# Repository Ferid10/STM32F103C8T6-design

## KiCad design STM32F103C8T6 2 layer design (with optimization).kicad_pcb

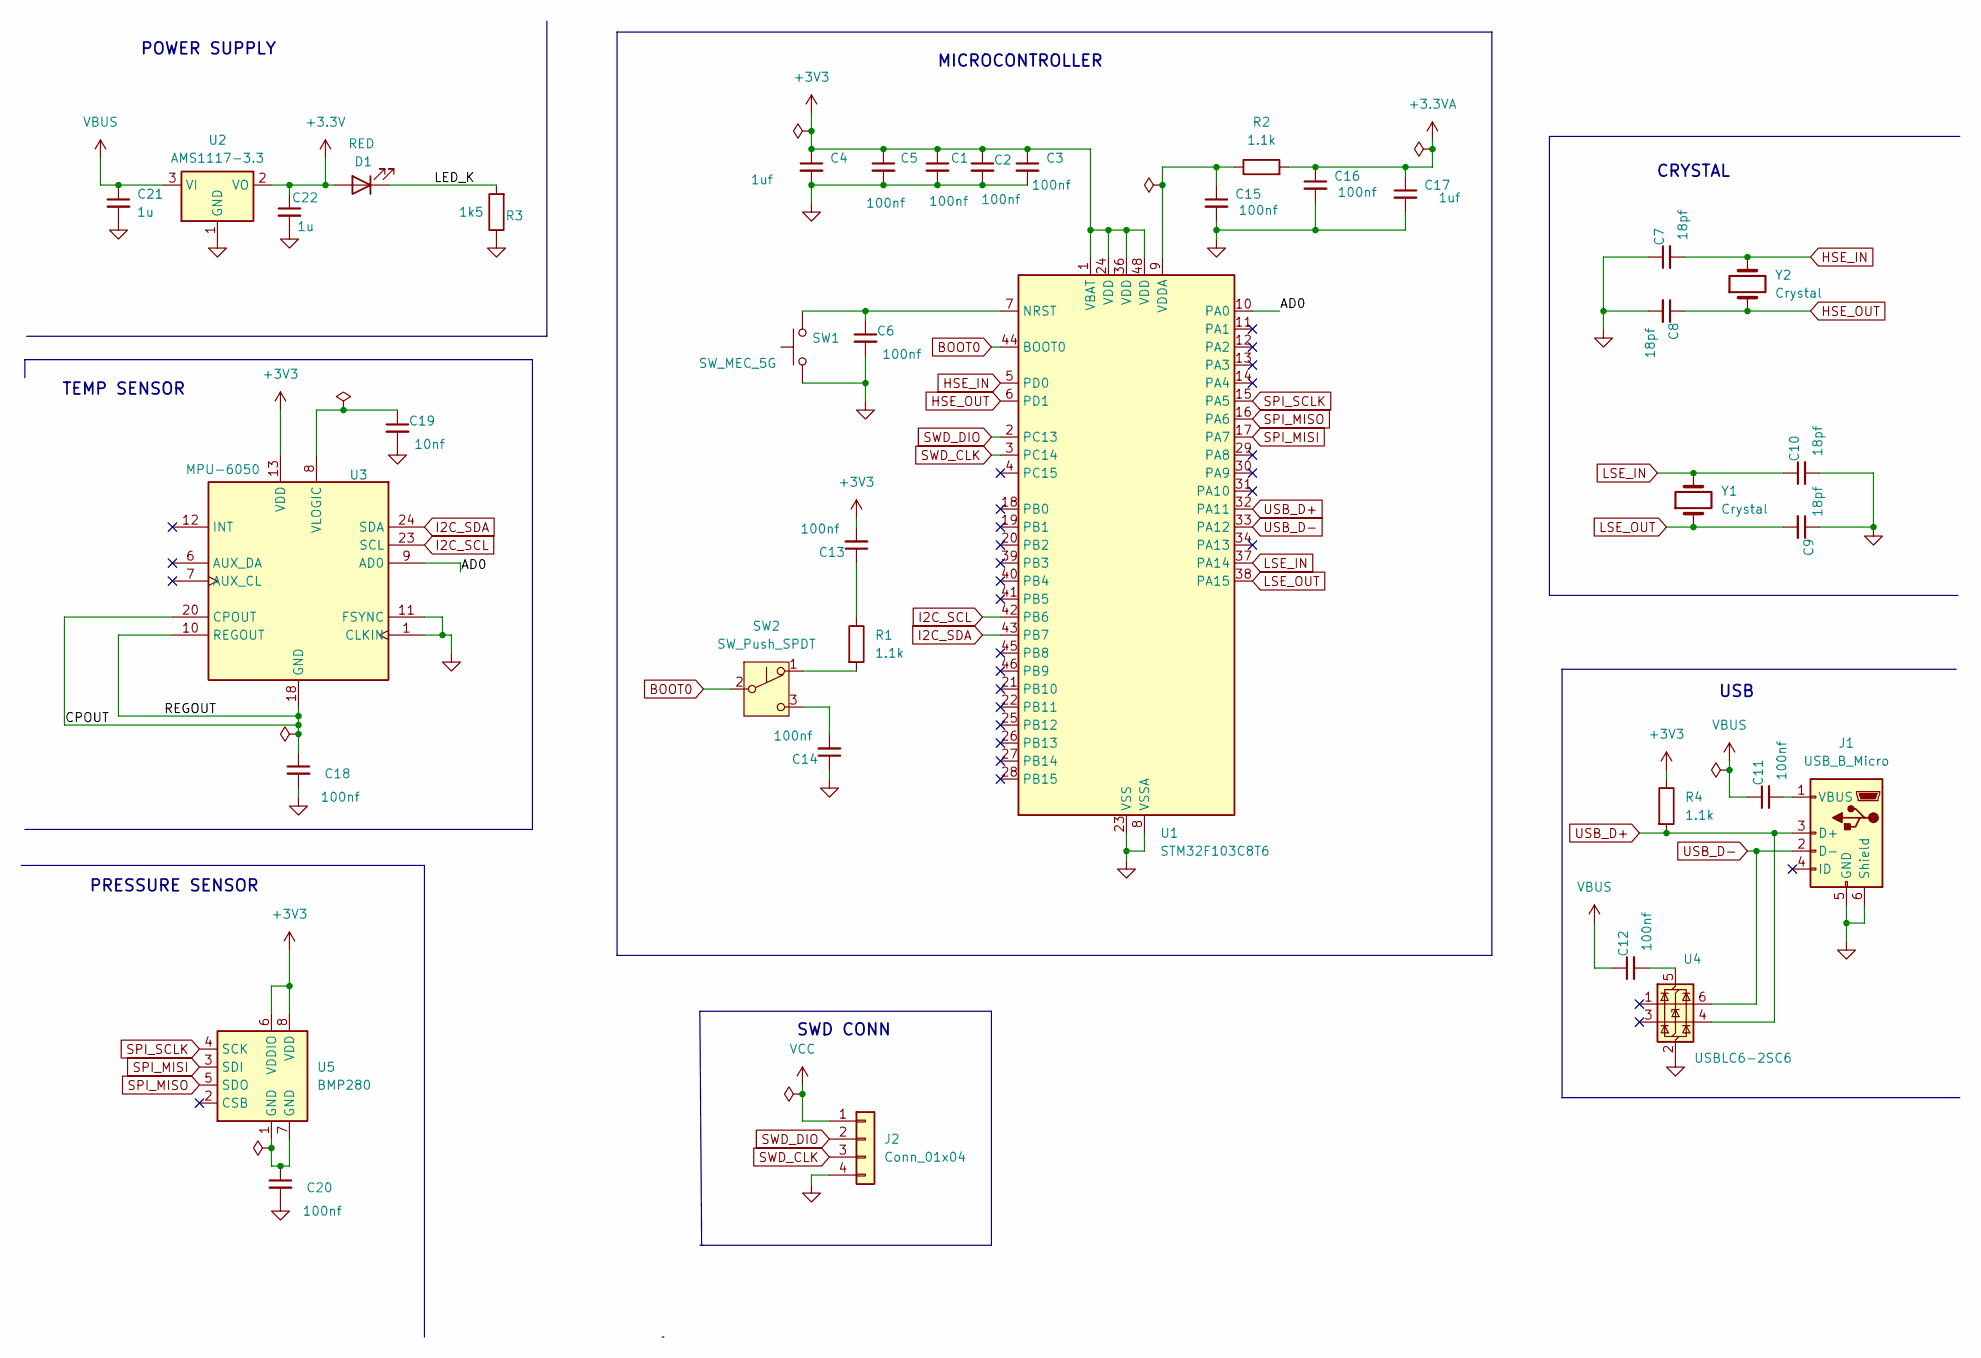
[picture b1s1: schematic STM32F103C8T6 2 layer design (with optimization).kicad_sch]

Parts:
C1, C2, C3, C5, C6, C11, C12, C13, C14, C15, C16: 100nf; C_01005_0402Metric
C4, C17: 1uf; C_0201_0603Metric
C7, C8, C9, C10: 18pf; C_01005_0402Metric
C18, C20: 100nf; C_0402_1005Metric
C19: 10nf; C_0402_1005Metric
C21, C22: 1u; C_0603_1608Metric
D1: RED; LED_2512_6332Metric
J1: USB_B_Micro; USB_Mini-B_Lumberg_2486_01_Horizontal
J2: Conn_01x04; PinHeader_1x04_P2.54mm_Vertical
R1, R2, R4: 1.1k; R_0402_1005Metric
R3: 1k5; R_01005_0402Metric
SW1: SW_MEC_5G; SW_MEC_5GSH9
SW2: SW_Push_SPDT; SW_DIP_SPSTx01_Slide_Copal_CVS-01xB_W5.9mm_P1mm
U1: STM32F103C8T6; LQFP-48_7x7mm_P0.5mm
U2: AMS1117-3.3; SOT-223-3_TabPin2
U3: MPU-6050; InvenSense_QFN-24_4x4mm_P0.5mm
U4: USBLC6-2SC6; SOT-23-6
U5: BMP280; Bosch_LGA-8_2x2.5mm_P0.65mm_ClockwisePinNumbering
Y1, Y2: Crystal; Crystal_SMD_5032-2Pin_5.0x3.2mm

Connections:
+3.3V: C22.1, D1.2 (A), U2.2 (VO)
+3.3VA: C16.1, C17.1, R2.2
+3V3: C1.1, C2.1, C3.1, C4.1, C5.1, C13.2, R4.1, U1.1 (VBAT), U1.24 (VDD), U1.36 (VDD), U1.48 (VDD), U3.13 (VDD), U5.6 (VDDIO), U5.8 (VDD)
/AD0: U1.10 (PA0), U3.9 (AD0)
/CPOUT: C18.1, U3.10 (REGOUT), U3.18 (GND), U3.20 (CPOUT)
/LED_K: D1.1 (K), R3.2
BOOT0: SW2.2 (B), U1.44 (BOOT0)
GND: C1.2, C2.2, C3.2, C4.2, C5.2, C6.2, C7.1, C8.2, C9.1, C10.2, C14.1, C15.2, C16.2, C17.2, C18.2, C19.2, C20.2, C21.2, C22.2, J1.5 (GND), J1.6 (Shield), J2.4, R3.1, SW1.1 (A), SW1.2 (A), U1.8 (VSSA), U1.23 (VSS), U1.35 (VSS), U1.47 (VSS), U2.1 (GND), U3.1 (CLKIN), U3.11 (FSYNC), U4.2 (GND)
HSE_IN: C7.2, U1.5 (PD0), Y2.2
HSE_OUT: C8.1, U1.6 (PD1), Y2.1
I2C_SCL: U1.42 (PB6), U3.23 (SCL)
I2C_SDA: U1.43 (PB7), U3.24 (SDA)
LSE_IN: C10.1, U1.37 (PA14), Y1.2
LSE_OUT: C9.2, U1.38 (PA15), Y1.1
unnamed: C13.1, R1.1
unnamed: C20.1, U5.1 (GND), U5.7 (GND)
unnamed: C11.2, J1.1 (VBUS)
unnamed: R1.2, SW2.1 (A)
unnamed: C14.2, SW2.3 (C)
unnamed: C6.1, SW1.3 (B), SW1.4 (B), U1.7 (NRST)
unnamed: C15.1, R2.1, U1.9 (VDDA)
unnamed: C19.1, U3.8 (VLOGIC)
unnamed: C12.2, U4.5 (VBUS)
SPI_MISI: U1.17 (PA7), U5.3 (SDI)
SPI_MISO: U1.16 (PA6), U5.5 (SDO)
SPI_SCLK: U1.15 (PA5), U5.4 (SCK)
SWD_CLK: J2.3, U1.3 (PC14)
SWD_DIO: J2.2, U1.2 (PC13)
USB_D+: J1.3 (D+), R4.2, U1.32 (PA11), U4.4 (I/O2)
USB_D-: J1.2 (D-), U1.33 (PA12), U4.6 (I/O1)
VBUS: C11.1, C12.1, C21.1, U2.3 (VI)
VCC: J2.1

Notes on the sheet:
MICROCONTROLLER
CRYSTAL
POWER SUPPLY
SWD CONN
TEMP SENSOR
PRESSURE SENSOR
USB

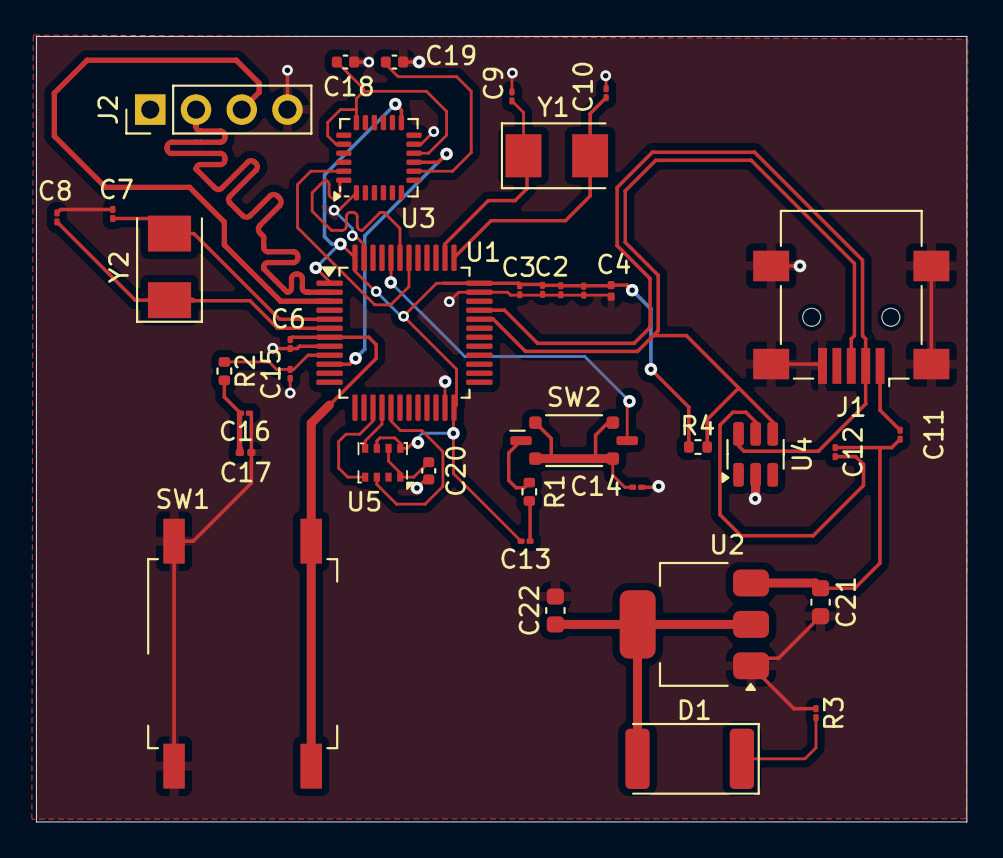
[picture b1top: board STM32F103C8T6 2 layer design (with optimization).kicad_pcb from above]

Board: 2 copper layers, 51.7 x 43.6 mm, 38 parts (0 on the bottom side), 31 nets.
